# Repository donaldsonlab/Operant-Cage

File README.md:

# Operant-Cage

This repository houses all of the hardware and software documents necessary for designing, manufacturing, and operating the operant cage developed by the Donaldson Lab at the University of Colorado - Boulder.

Its cool stuff.

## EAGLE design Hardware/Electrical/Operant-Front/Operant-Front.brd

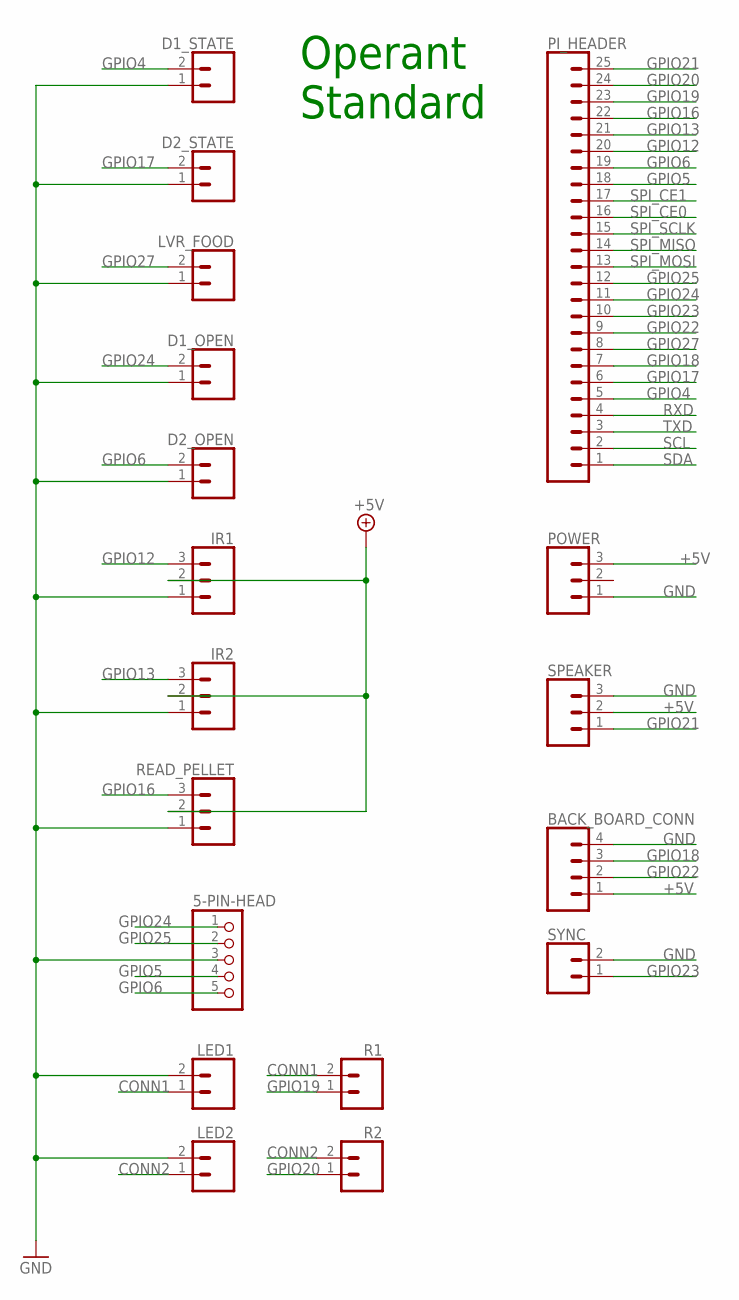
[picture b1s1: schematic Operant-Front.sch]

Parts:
5-PIN-HEAD: PINHD-1X5; 1X05
BACK_BOARD_CONN: CONN_04JST-PTH; JST-4-PTH
D1_OPEN, D1_STATE, D2_OPEN, D2_STATE: CONN_02JST-PTH-2; JST-2-PTH
IR1, IR2: CONN_03JST-PTH; JST-3-PTH
LED1, LED2: CONN_02; 1X02
LVR_FOOD: CONN_02JST-PTH-2; JST-2-PTH
PI_HEADER: CONN_25; 1X25
POWER: CONN_03; 1X03
R1, R2: CONN_02; 1X02
READ_PELLET: CONN_03JST-PTH; JST-3-PTH
SPEAKER: CONN_03JST-PTH; JST-3-PTH
SYNC: CONN_02; 1X02

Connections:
+5V: BACK_BOARD_CONN.1, IR1.2, IR2.2, POWER.3, READ_PELLET.2, SPEAKER.2
CONN1: LED1.1, R1.2
CONN2: LED2.1, R2.2
GND: 5-PIN-HEAD.3, BACK_BOARD_CONN.4, D1_OPEN.1, D1_STATE.1, D2_OPEN.1, D2_STATE.1, IR1.1, IR2.1, LED1.2, LED2.2, LVR_FOOD.1, POWER.1, READ_PELLET.1, SPEAKER.3, SYNC.2
GPIO4: D1_STATE.2, PI_HEADER.5
GPIO5: 5-PIN-HEAD.4, PI_HEADER.18
GPIO6: 5-PIN-HEAD.5, D2_OPEN.2, PI_HEADER.19
GPIO12: IR1.3, PI_HEADER.20
GPIO13: IR2.3, PI_HEADER.21
GPIO16: PI_HEADER.22, READ_PELLET.3
GPIO17: D2_STATE.2, PI_HEADER.6
GPIO18: BACK_BOARD_CONN.3, PI_HEADER.7
GPIO19: PI_HEADER.23, R1.1
GPIO20: PI_HEADER.24, R2.1
GPIO21: PI_HEADER.25, SPEAKER.1
GPIO22: BACK_BOARD_CONN.2, PI_HEADER.9
GPIO23: PI_HEADER.10, SYNC.1
GPIO24: 5-PIN-HEAD.1, D1_OPEN.2, PI_HEADER.11
GPIO25: 5-PIN-HEAD.2, PI_HEADER.12
GPIO27: LVR_FOOD.2, PI_HEADER.8
RXD: PI_HEADER.4
SCL: PI_HEADER.2
SDA: PI_HEADER.1
SPI_CE0: PI_HEADER.16
SPI_CE1: PI_HEADER.17
SPI_MISO: PI_HEADER.14
SPI_MOSI: PI_HEADER.13
SPI_SCLK: PI_HEADER.15
TXD: PI_HEADER.3

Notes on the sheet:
Operant Standard

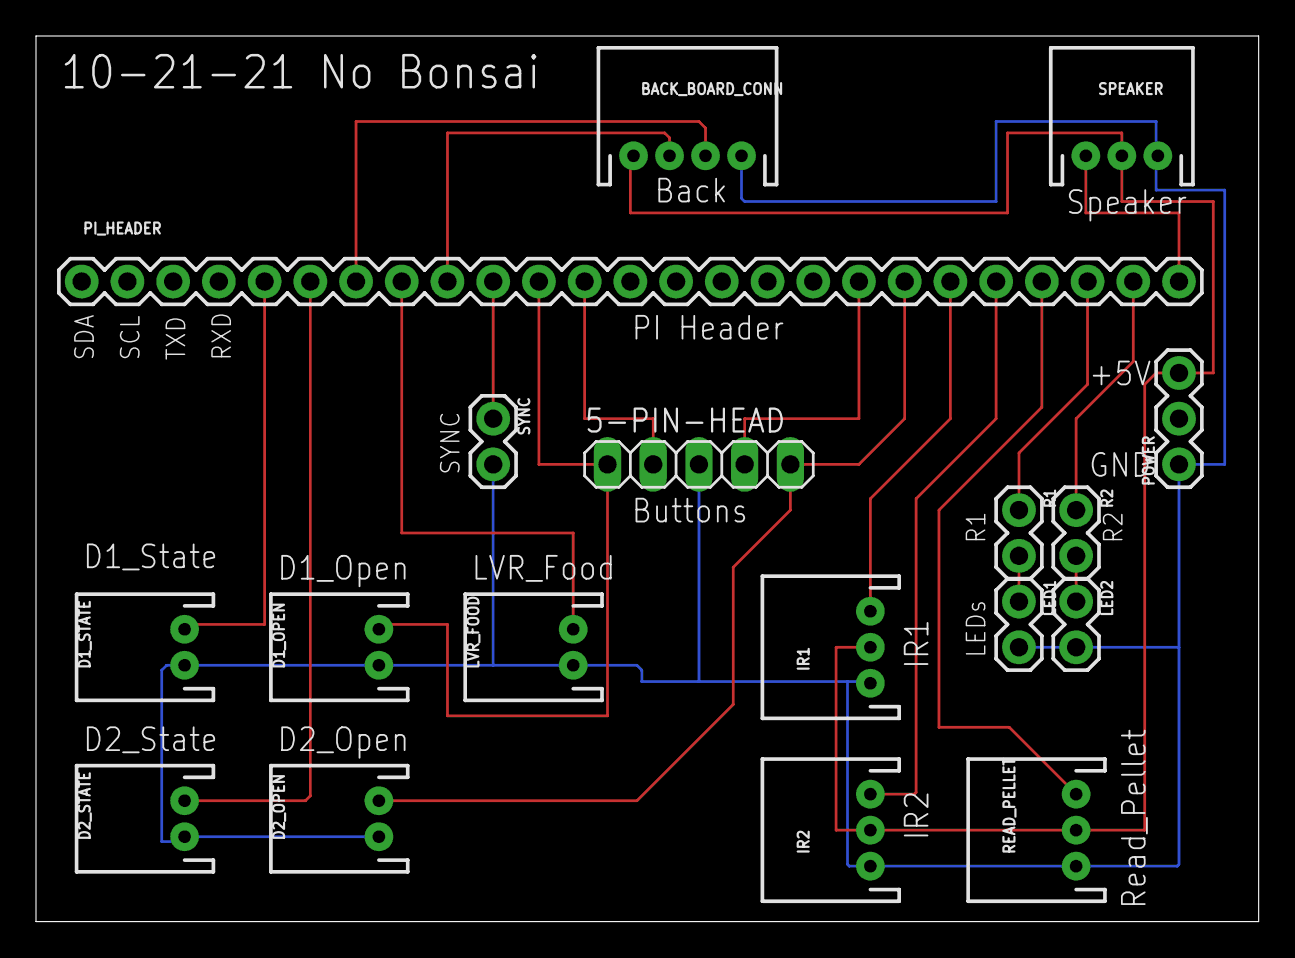
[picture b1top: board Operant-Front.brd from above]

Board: 2 copper layers, 67.9 x 49.2 mm, 18 parts (0 on the bottom side), 20 nets.

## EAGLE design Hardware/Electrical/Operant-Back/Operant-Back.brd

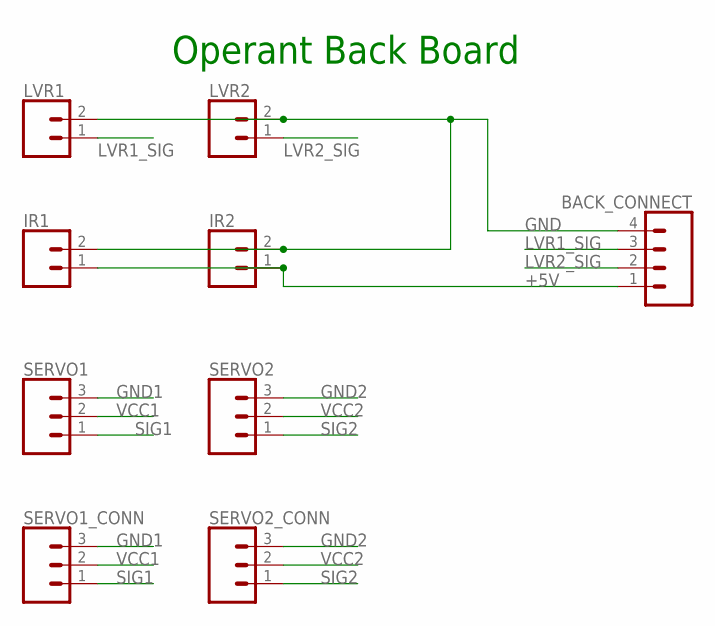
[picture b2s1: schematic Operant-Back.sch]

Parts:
BACK_CONNECT: CONN_04JST-PTH; JST-4-PTH
IR1, IR2: CONN_02JST-PTH-2; JST-2-PTH
LVR1, LVR2: CONN_02JST-PTH-2; JST-2-PTH
SERVO1, SERVO2: CONN_03; 1X03
SERVO1_CONN, SERVO2_CONN: CONN_03JST-PTH; JST-3-PTH

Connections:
+5V: BACK_CONNECT.1, IR1.1, IR2.1
GND: BACK_CONNECT.4, IR1.2, IR2.2, LVR1.2, LVR2.2
GND1: SERVO1.3, SERVO1_CONN.3
GND2: SERVO2.3, SERVO2_CONN.3
LVR1_SIG: BACK_CONNECT.3, LVR1.1
LVR2_SIG: BACK_CONNECT.2, LVR2.1
SIG1: SERVO1.1, SERVO1_CONN.1
SIG2: SERVO2.1, SERVO2_CONN.1
VCC1: SERVO1.2, SERVO1_CONN.2
VCC2: SERVO2.2, SERVO2_CONN.2

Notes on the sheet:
Operant Back Board

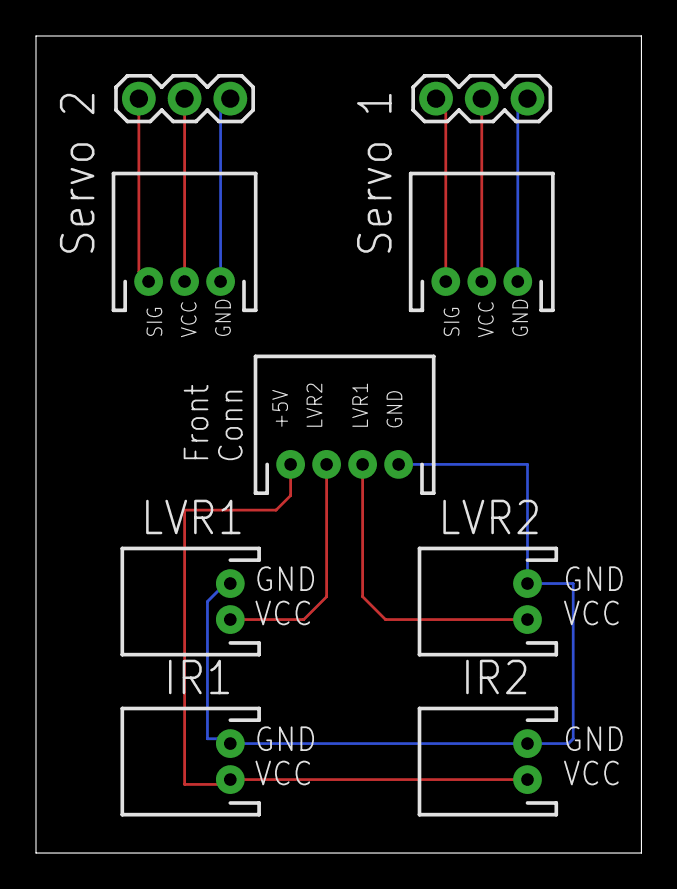
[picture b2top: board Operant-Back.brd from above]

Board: 2 copper layers, 33.6 x 45.4 mm, 9 parts (0 on the bottom side), 10 nets.

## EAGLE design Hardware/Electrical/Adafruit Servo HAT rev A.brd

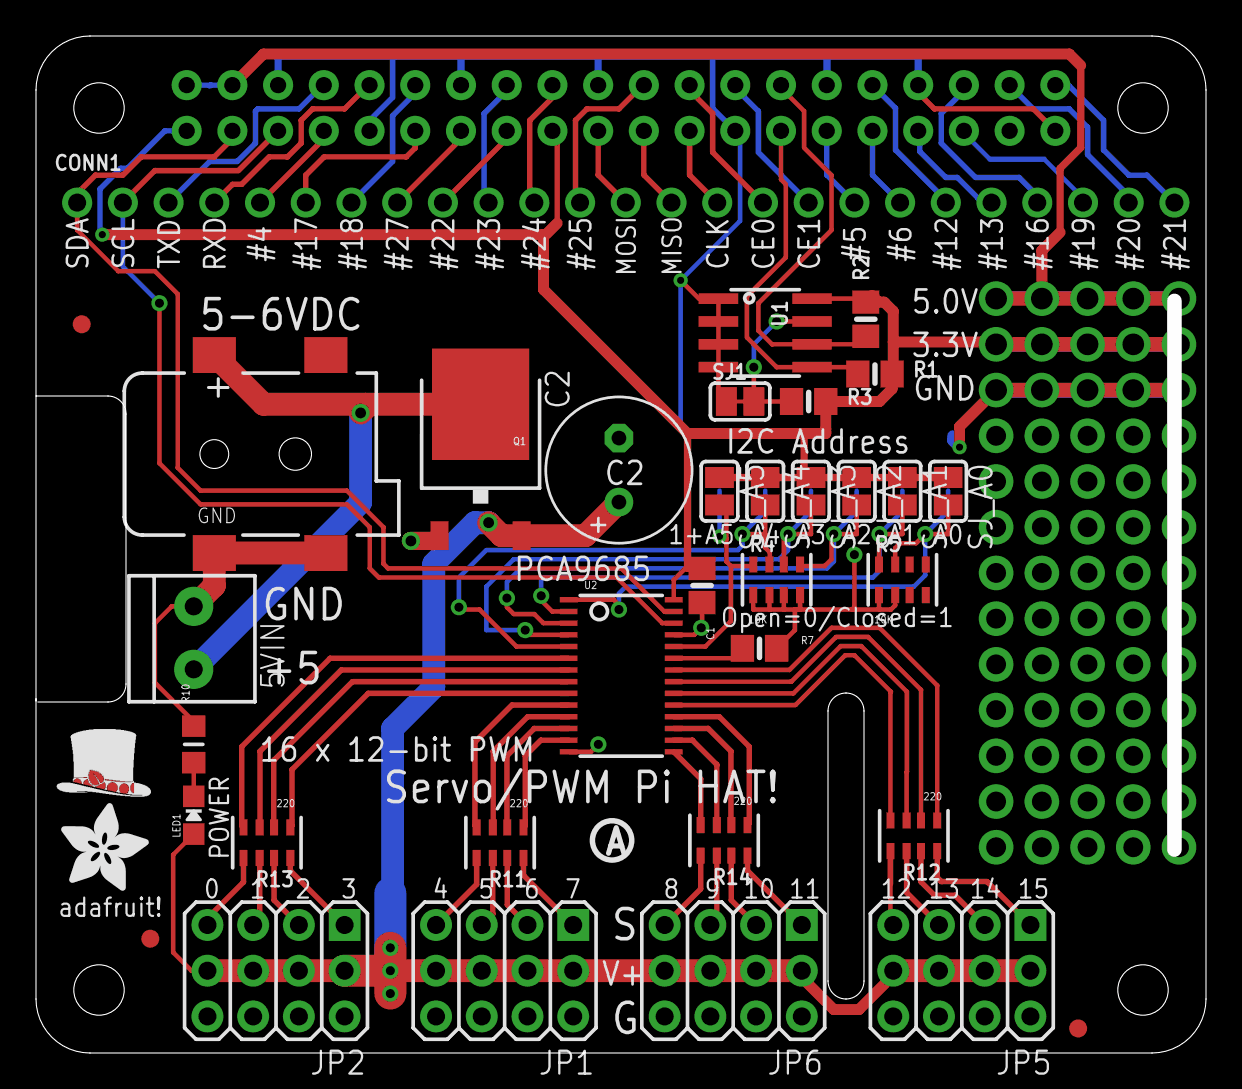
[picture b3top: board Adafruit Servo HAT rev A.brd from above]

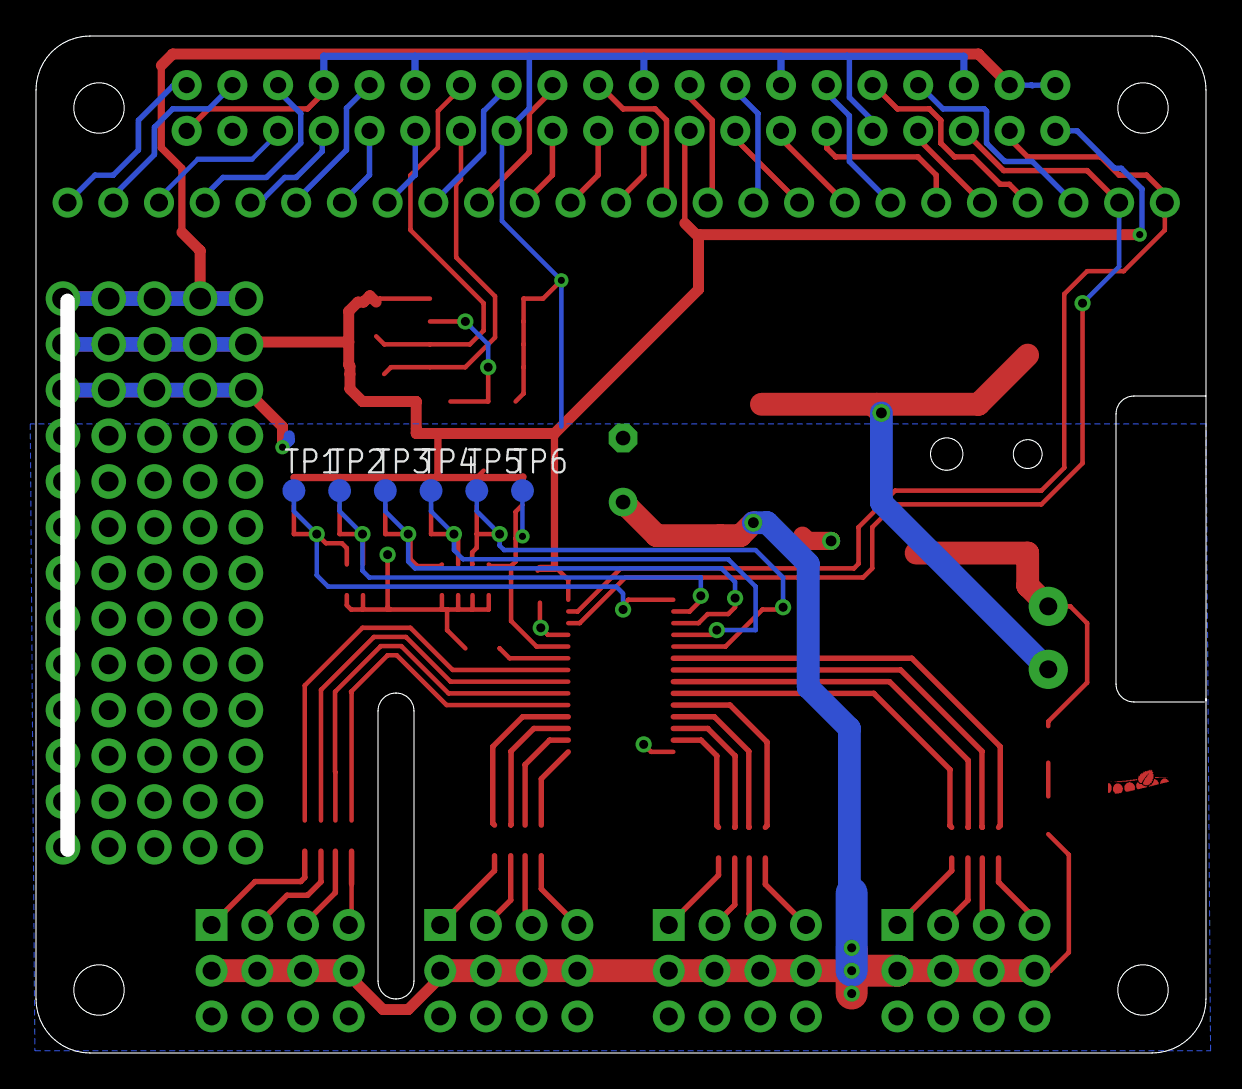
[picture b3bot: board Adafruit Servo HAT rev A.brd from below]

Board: 2 copper layers, 64.2 x 55.7 mm, 44 parts (6 on the bottom side), 73 nets.

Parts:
5VIN: 3.5mm term; TERMBLOCK_1X2-3.5MM
C1: 10uF; 0805-NO
C2: E3,5-8
CONN1: HEADER-1X25; 1X25_ROUND_70MIL
FID1, FID2, FID3: FIDUCIAL""; FIDUCIAL_1MM
JP1, JP2, JP5, JP6: 3X04
LED1: GREEN; CHIPLED_0805_NOOUTLINE
Q1: AOD417; TO252
R1, R2, R3: 3.9K; 0805-NO
R4, R5: 10K; RESPACK_4X0603
R7: 10K; 0805-NO
R10: 470; _0805MP
R11, R12, R13, R14: 220; RESPACK_4X0603
RPI1: RASPBERRYPI_BPLUS_HATSLOTS; PI_HAT_SLOTS
SJ1: WP; SOLDERJUMPER_CLOSEDWIRE
SJ_A0, SJ_A1, SJ_A2, SJ_A3, SJ_A4, SJ_A5: SOLDERJUMPER_REFLOW_NOPASTE
TP1, TP2, TP3, TP4, TP5, TP6: TPB1,27; B1,27
U1: CAT24C32; SOIC8_150MIL
U2: PCA9685; TSSOP28
U$5: PIHATLOGO
U$6: PCBFEAT-REV-056
U$51: ADAFRUIT_5MM
X1: 2.1mm SMT; DCJACK_2MM_SMT

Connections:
3.3V: C1.1, R1.2, R2.2, R3.2, RPI1.1, RPI1.17, SJ_A0.1, SJ_A1.1, SJ_A2.1, SJ_A3.1, SJ_A4.1, SJ_A5.1, U1.8, U2.28
5.0V: RPI1.2, RPI1.4
+5V: C2.+, JP1.2, JP1.5, JP1.8, JP1.11, JP2.2, JP2.5, JP2.8, JP2.11, JP5.2, JP5.5, JP5.8, JP5.11, JP6.2, JP6.5, JP6.8, JP6.11, LED1.A, Q1.2
A0: R5.7, SJ_A0.2, TP1.TP, U2.1
A1: R5.8, SJ_A1.2, TP2.TP, U2.2
A2: R4.5, SJ_A2.2, TP3.TP, U2.3
A3: R4.6, SJ_A3.2, TP4.TP, U2.4
A4: R4.7, SJ_A4.2, TP5.TP, U2.5
A5: R4.8, SJ_A5.2, TP6.TP, U2.24
EECLK: R2.1, RPI1.28, U1.6
EEDATA: R1.1, RPI1.27, U1.5
GND: 5VIN.2, C1.2, C2.-, JP1.3, JP1.6, JP1.9, JP1.12, JP2.3, JP2.6, JP2.9, JP2.12, JP5.3, JP5.6, JP5.9, JP5.12, JP6.3, JP6.6, JP6.9, JP6.12, Q1.1, R4.1, R4.2, R4.3, R4.4, R5.1, R5.2, R7.2, R10.2, RPI1.6, RPI1.9, RPI1.14, RPI1.20, RPI1.25, RPI1.30, RPI1.34, RPI1.39, SJ1.1, U1.1, U1.2, U1.3, U1.4, U2.14, U2.25, X1.GND, X1.GNDBREAK
GPIO4: CONN1.5, RPI1.7
GPIO5: CONN1.18, RPI1.29
GPIO6: CONN1.19, RPI1.31
GPIO12: CONN1.20, RPI1.32
GPIO13: CONN1.21, RPI1.33
GPIO16: CONN1.22, RPI1.36
GPIO17: CONN1.6, RPI1.11
GPIO18: CONN1.7, RPI1.12
GPIO19: CONN1.23, RPI1.35
GPIO20: CONN1.24, RPI1.38
GPIO21: CONN1.25, RPI1.40
GPIO22: CONN1.9, RPI1.15
GPIO23: CONN1.10, RPI1.16
GPIO24: CONN1.11, RPI1.18
GPIO25: CONN1.12, RPI1.22
GPIO27: CONN1.8, RPI1.13
unnamed: R3.1, SJ1.2, U1.7
unnamed: LED1.C, R10.1
unnamed: JP1.4, R11.7
unnamed: JP1.1, R11.8
unnamed: JP1.7, R11.6
unnamed: JP1.10, R11.5
unnamed: JP2.1, R13.8
unnamed: JP2.4, R13.7
unnamed: JP2.7, R13.6
unnamed: JP2.10, R13.5
unnamed: JP6.10, R14.5
unnamed: JP6.7, R14.6
unnamed: JP6.4, R14.7
unnamed: JP6.1, R14.8
unnamed: JP5.10, R12.5
unnamed: JP5.7, R12.6
unnamed: JP5.4, R12.7
unnamed: JP5.1, R12.8
OE: R7.1, U2.23
PWM0: R13.4, U2.6
PWM1: R13.3, U2.7
PWM2: R13.2, U2.8
PWM3: R13.1, U2.9
PWM4: R11.4, U2.10
PWM5: R11.3, U2.11
PWM6: R11.2, U2.12
PWM7: R11.1, U2.13
PWM8: R14.4, U2.15
PWM9: R14.3, U2.16
PWM10: R14.2, U2.17
PWM11: R14.1, U2.18
PWM12: R12.4, U2.19
PWM13: R12.3, U2.20
PWM14: R12.2, U2.21
PWM15: R12.1, U2.22
PWRIN: 5VIN.1, Q1.3, X1.PWR
RXD: CONN1.4, RPI1.10
SCL: CONN1.2, RPI1.5, U2.26
SDA: CONN1.1, RPI1.3, U2.27
SPI_CE0: CONN1.16, RPI1.24
SPI_CE1: CONN1.17, RPI1.26
SPI_MISO: CONN1.14, RPI1.21
SPI_MOSI: CONN1.13, RPI1.19
SPI_SCLK: CONN1.15, RPI1.23
TXD: CONN1.3, RPI1.8

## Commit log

2021-05-10 Initial Upload
2021-05-13 Soundproof Box design
2021-06-29 Minor Updates
    Minor Updates
    -Modify door gear rack
    - Add extra height to walls
    - Include Operant V1
    - Adjust wall and floor thickness
    - Other small changes
2021-06-29 Accidental Deletion
2021-07-09 Preference Height Updates
2021-07-13 Modify Door Height Extension
2021-07-21 Merge
2021-08-03 Added RPI_operant as a submodule to reference for any test scripts and whatnot
2021-08-04 Submodule update
2021-08-09 submodule changes
2021-08-17 Merge
    Creation of electronic components
2021-08-26 Added Electrical Docs
2021-08-31 schematics
2021-09-07 Schematic
2021-09-09 post-processing script fro bonsai
2021-09-09 submodule checkout
2021-09-09 added bonsai script
2021-09-10 switched to main RPI_operant
2021-09-23 Updated csv parser
2021-10-12 PCB Designs
2021-10-14 Final version for standard operant board
2021-10-19 Added gitignore
2021-10-19 Operant Front Board
2021-10-19 Added dims
2021-10-19 Added the Bonsai variation
2021-10-21 Updated boards
2021-10-21 Extended Board
2022-02-03 Last commit from PC
2022-06-01 Add lower lever
2022-06-01 door updates
2022-06-01 Fully assembly debugging
2022-06-06 end of week
2022-08-15 end of day
2022-10-21 Manufacturing updates
2022-11-23 manufacturing files added for short levers
2023-02-03 end of week - added gerber files for electrical manufacturing
2023-03-07 Electrical files
2023-05-15 Test commit
2023-05-16 Updated Lever Docs
2023-05-31 Added smaller interaction box
2023-06-13 Added food dispenser
2023-06-13 merging
2023-06-13 merging part 2
2023-06-13 merging part 3
2023-06-19 Updating V3
2023-07-24 End of Work - Ryan Cameron
2023-07-26 update 20230726
2024-06-27 6/27 v3 updates
2024-06-27 6/27 update
2024-09-05 Drawing + Printing Files for new operant box (for October 2024) Files uploaded 2024-09-05
2024-12-18 Lena - end of work

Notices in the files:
parts and their libraries:
microbuilder: This work is placed in the public domain, and may be freely used for commercial and non-commercial work with the following conditions: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
SparkFun-Connectors: Licensing: Creative Commons ShareAlike 4.0 International - https://creativecommons.org/licenses/by-sa/4.0
